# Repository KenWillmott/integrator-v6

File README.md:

# integrator-v6
guitar pickup test integrator V6.x

This hardware version of the integrator replaces the much older V5.8/V5.9 integrator.
General information about the integrator project is found here, along with the older design files:

https://github.com/KenWillmott/integrator/wiki

The newer V6.0 is a smaller, more integrated version of the same circuit, with upgraded components. It is possible to order a build from the factory. The BOM is a complete build, with all components, including switches and connectors. It is a fully functional integrator, needs only to be calibrated to work. A case or enclosure is recommended, So far an aluminum and an acrylic case have been used. It is possible to special order the boards without switches and connectors by noting them DNP on a modified BOM.

Complete BOM: [BOM-V601(2025-04-11).xls](https://github.com/KenWillmott/integrator-v6/blob/main/BOM-V601(2025-04-11).xls)

The project is listed at the PCBWay site, you can place an multi-board order there by following the ordering links and specifying "PCB+Assembly".
[PCBWay order link](https://www.pcbway.com/project/shareproject/W22492BSH46_integrator_V6_Gerber_e358a0f5.html)

Note that you can produce the PCB by any method, by importing the KiCad project and exporting the necessary fabrication files.

## Important!:
Some manufacturers and myself, have had problems sourcing the 3-way switch. So I provided onboard solder jumper J1 to select between 3-way (100-SP3) and 2-way
(100-SP1) switches. If the 100-SP3 is available, PCB V6.02 will work with no modifications and PCB 6.03 requires a solder blob on J1. If the 100-SP1 must be used, PCB V6.03 will work with no modifications and PCB V6.02 requires that C1 be either removed or not placed during production. Using the ON-ON functioning of the 100-SP1 will sacrifice the ability to make approximate inductance measurements, while preserving the no-load and loaded settings (which are the most important ones).

From a pure manufacturing point of view, the combinations

V6.02 --> 100SP3T1B4M7QE

V6.03 --> 100SP1T1B4M7QE

are preferred, since those configurations require no board or BOM modifications. However, V6.02 may be deprecated soon, since it's easier to modify V6.03 for either switch type.

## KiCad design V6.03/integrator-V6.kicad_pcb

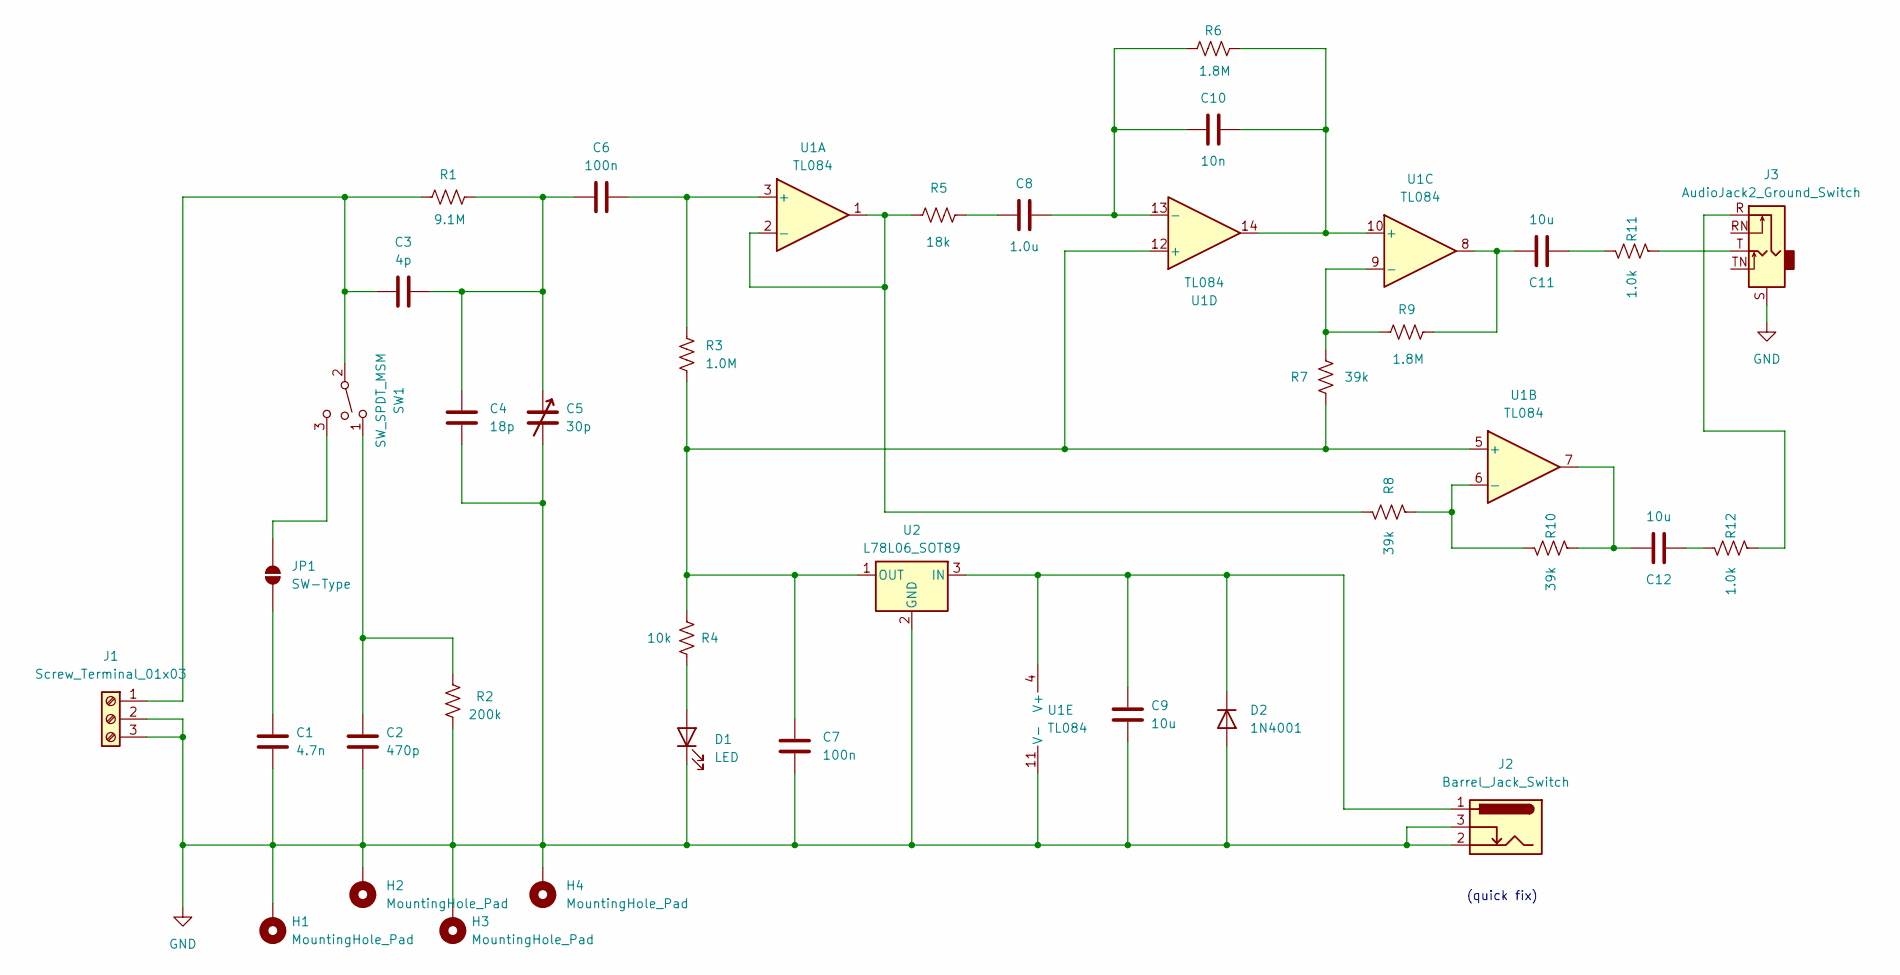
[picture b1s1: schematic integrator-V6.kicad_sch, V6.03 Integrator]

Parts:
C1: 4.7n; C_0603_1608Metric
C2: 470p; C_0603_1608Metric
C3: 4p; C_0603_1608Metric
C4: 18p; C_0603_1608Metric
C5: 30p; C_Trimmer_Murata_TZB4-A
C6, C7: 100n; C_0603_1608Metric
C8: 1.0u; C_0603_1608Metric
C9, C11, C12: 10u; C_0805_2012Metric
C10: 10n; C_0603_1608Metric
D1: LED; LED_0603_1608Metric
D2: 1N4001; D_SOD-123
H1, H2, H3, H4: MountingHole_Pad; MountingHole_3.2mm_M3_DIN965_Pad
J1: Screw_Terminal_01x03; TerminalBlock_4Ucon_1x03_P3.50mm_Vertical
J2: Barrel_Jack_Switch; BarrelJack_GCT_DCJ200-10-A_Horizontal
J3: AudioJack2_Ground_Switch; Jack_3.5mm_CUI_SJ1-3525N_Horizontal
JP1: SW-Type; SolderJumper-2_P1.3mm_Open_RoundedPad1.0x1.5mm
R1: 9.1M; R_0603_1608Metric
R2: 200k; R_0603_1608Metric
R3: 1.0M; R_0603_1608Metric
R4: 10k; R_0603_1608Metric
R5: 18k; R_0603_1608Metric
R6, R9: 1.8M; R_0603_1608Metric
R7, R8, R10: 39k; R_0603_1608Metric
R11, R12: 1.0k; R_0603_1608Metric
SW1: SW_SPDT_MSM; MTS-103 Switch
U1: TL084; SOIC-14_3.9x8.7mm_P1.27mm
U2: L78L06_SOT89; SOT-89-3

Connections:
GND: C1.2, C2.2, C4.1, C5.2, C7.2, C9.2, D1.1 (K), D2.2 (A), H1.1 (1_1), H2.1 (1_1), H3.1 (1_1), H4.1 (1_1), J1.2, J1.3, J2.2, J2.3, J3.S, R2.1, U1.11 (V-), U2.2 (GND)
unnamed: C2.1, R2.2, SW1.1
unnamed: C3.2, C4.2, C5.1, C6.2, R1.2
unnamed: C8.2, R5.1
unnamed: C11.1, R9.2, U1.8
unnamed: C11.2, R11.1
unnamed: C12.1, R10.2, U1.7
unnamed: C12.2, R12.1
unnamed: D1.2 (A), R4.2
unnamed: C9.1, D2.1 (K), J2.1, U1.4 (V+), U2.3 (IN)
unnamed: C3.1, J1.1, R1.1, SW1.2
unnamed: J3.R, R12.2
unnamed: J3.T, R11.2
unnamed: C1.1, JP1.1 (A)
unnamed: JP1.2 (B), SW1.3
unnamed: C6.1, R3.1, U1.3 (+)
unnamed: R5.2, R8.1, U1.1, U1.2 (-)
unnamed: C7.1, R3.2, R4.1, R7.2, U1.5 (+), U1.12 (+), U2.1 (OUT)
unnamed: R8.2, R10.1, U1.6 (-)
unnamed: C10.1, R6.2, U1.10 (+), U1.14
unnamed: R7.1, R9.1, U1.9 (-)
unnamed: C8.1, C10.2, R6.1, U1.13 (-)

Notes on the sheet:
(quick fix)

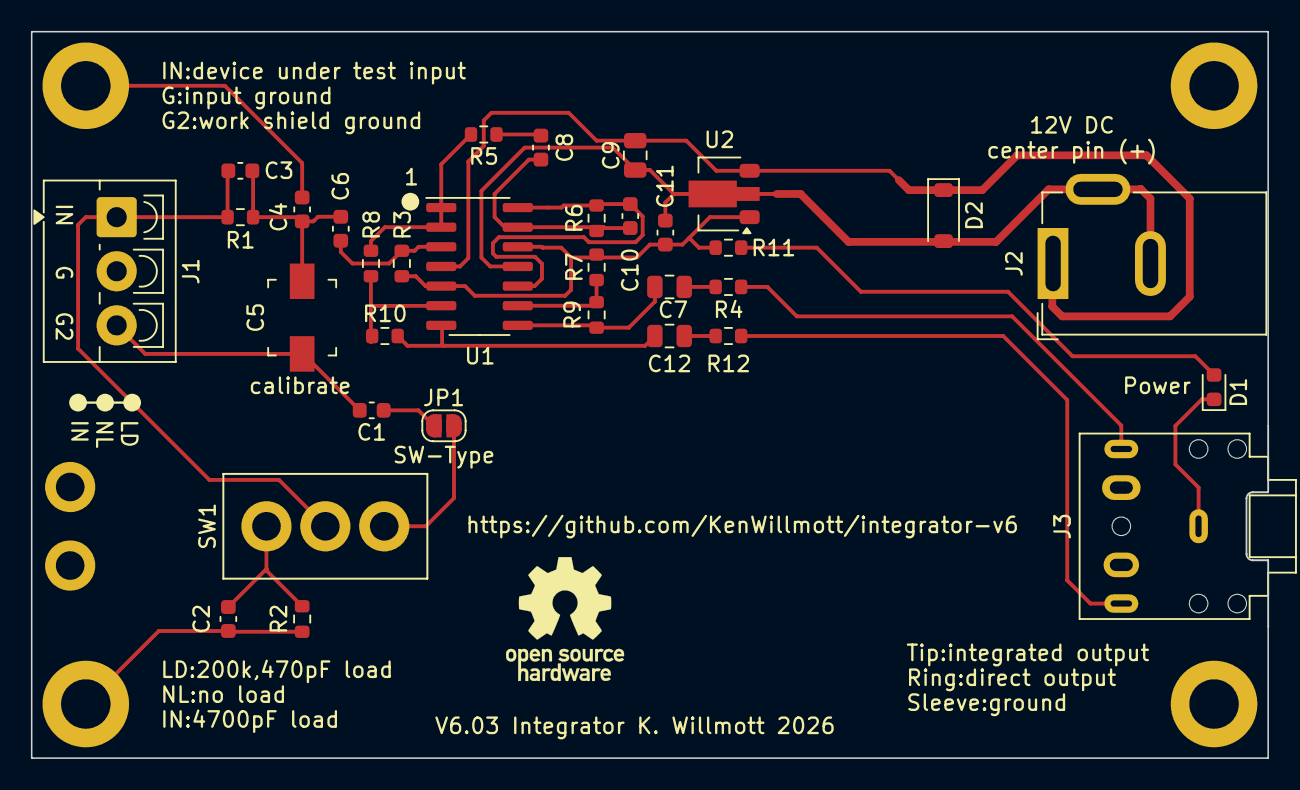
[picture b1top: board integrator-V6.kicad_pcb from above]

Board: 2 copper layers, 80.0 x 47.0 mm, 37 parts (0 on the bottom side), 22 nets.

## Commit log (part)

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2025-04-03 Create foo
2025-04-03 Add files via upload
    schematic
2025-11-10 Update README with details about integrator V6
    Added detailed information about the V6 integrator, including links to documentation and BOM details.
2025-11-10 Add BOM file reference to README
2025-11-10 Update README with BOM link and enclosure recommendation
2025-11-10 Update README with BOM details and ordering options
    Removed mention of two BOMs and clarified ordering options.
2025-11-10 Update README with PCB ordering and production info
    Added information about ordering and producing PCBs.
2025-11-10 Update PCBWay order link in README
